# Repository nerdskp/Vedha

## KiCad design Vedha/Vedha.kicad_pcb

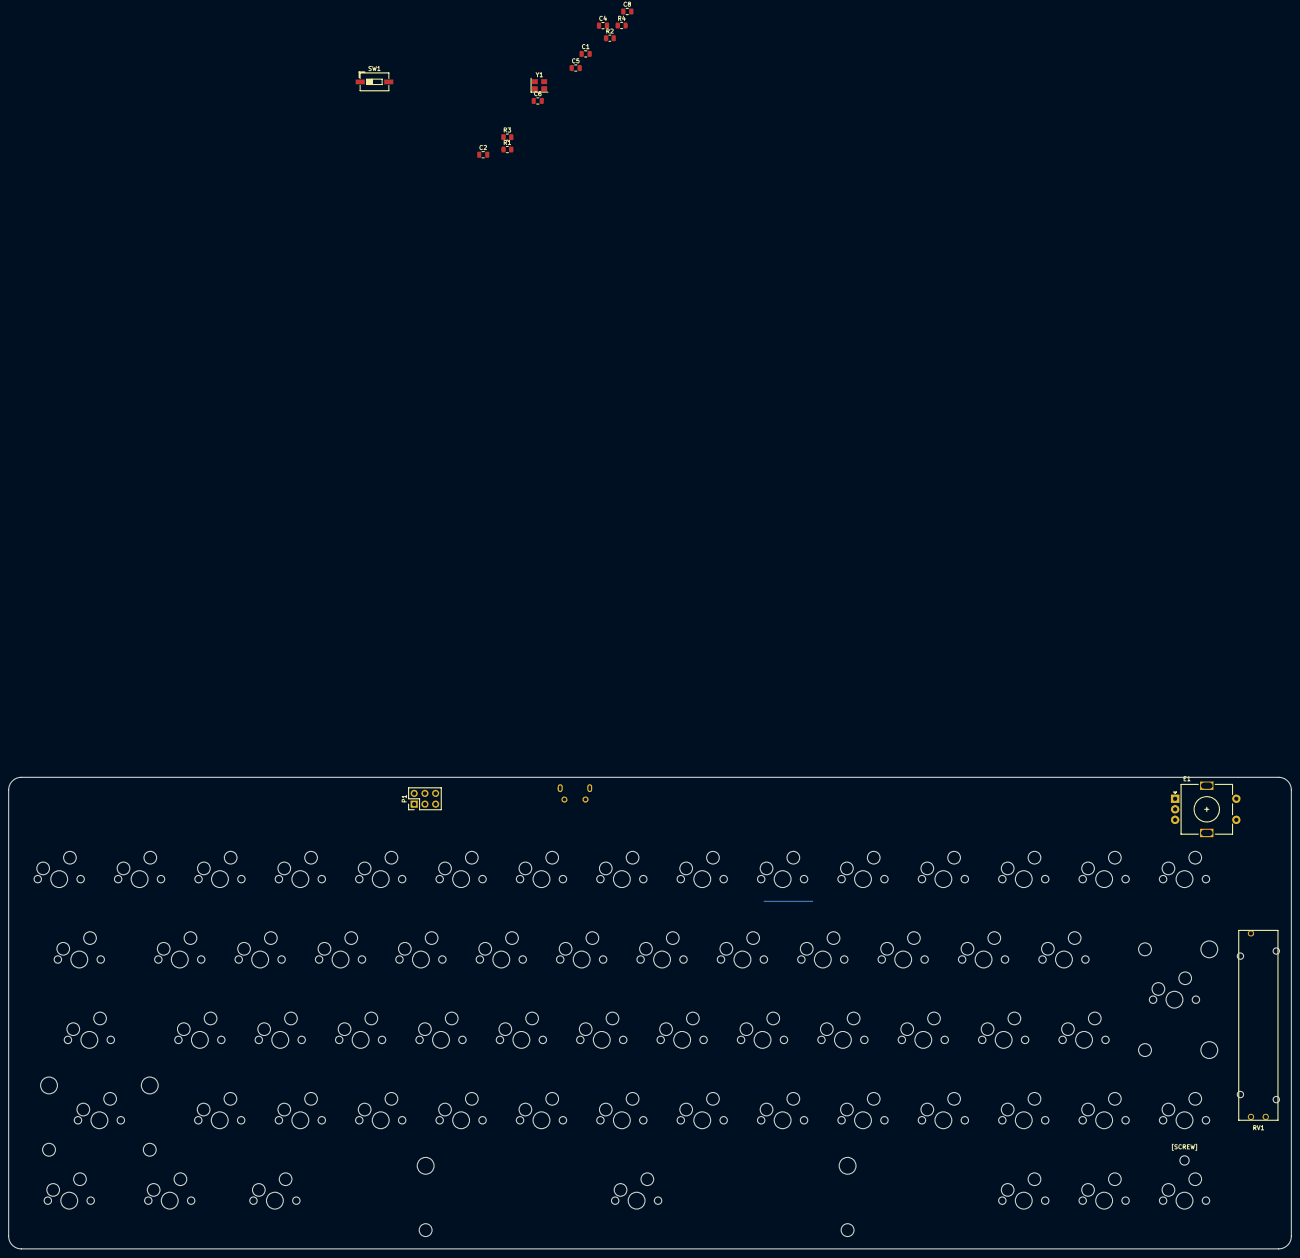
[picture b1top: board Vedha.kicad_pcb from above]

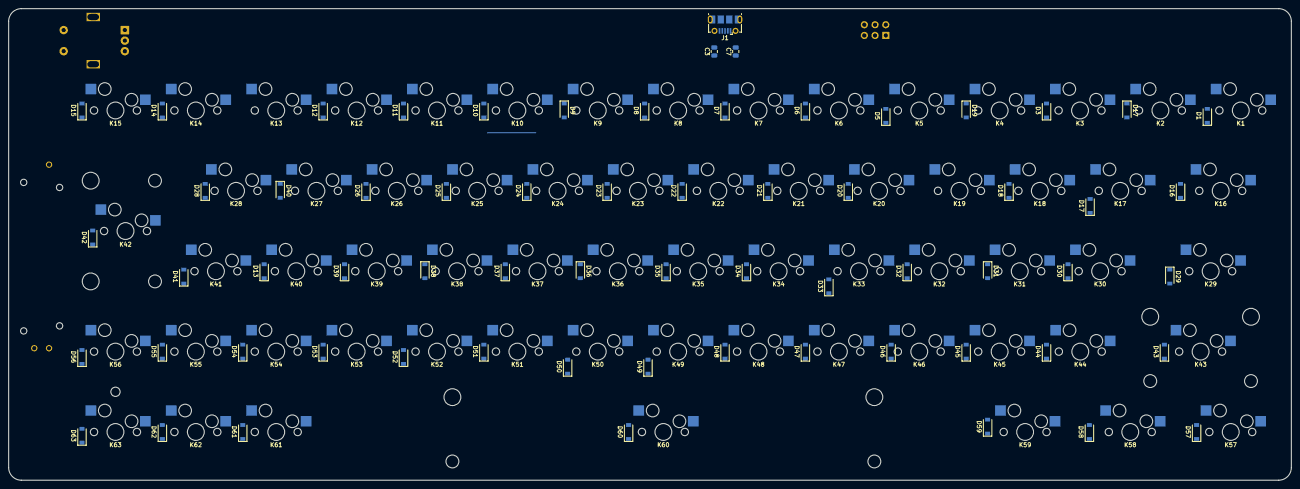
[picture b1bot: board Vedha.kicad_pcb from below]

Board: 2 copper layers, 304.0 x 111.8 mm, 143 parts (64 on the bottom side), 72 nets.

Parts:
C1, C2: 22p; C_0805_2012Metric
C3: 1u; C_0805_2012Metric
C4: 4.7u; C_0805_2012Metric
C5, C6, C7, C8: 100n; C_0805_2012Metric
D1, D3, D5, D6, D7, D8, D9, D10, D11, D12, D13, D14, D15, D16, D17, D17#2, D18, D19, D20, D21, D22, D23, D24, D25, D26, D28, D29, D30, D31, D32, D33, D34, D35, D36, D37, D38, D39, D40, D41, D42, D43, D44, D45, D46, D47, D48, D49, D50, D51, D52, D53, D54, D55, D56, D57, D58, D59, D60, D61, D62, D63: D; D_SOD-123
E1: Rotary_Encoder_Switch; RotaryEncoder_Alps_EC11E-Switch_Vertical_H20mm
J1: USB_B_Micro; USB_Micro-B_Molex-105017-0001
K1, K2, K3, K4, K5, K6, K7, K8, K9, K10, K11, K12, K13, K14, K15, K17, K18, K19, K20, K21, K22, K23, K24, K25, K26, K27, K28, K30, K31, K32, K33, K34, K35, K36, K37, K38, K39, K40, K41, K44, K45, K46, K47, K48, K49, K50, K51, K52, K53, K54, K55, K56, K61, K62, K63: KEYSW; MXOnly-1U-Hotswap
K16: KEYSW; MXOnly-1.5U-Hotswap
K29: KEYSW; MXOnly-1.75U-Hotswap
K42: KEYSW; MXOnly-ISO-Hotswap
K43: KEYSW; MXOnly-2U-Hotswap-ReversedStabilizers
K57, K58, K59: KEYSW; MXOnly-1.25U-Hotswap
K60: KEYSW; MXOnly-6.25U-Hotswap-ReversedStabilizers
P1: AVR-ISP-6; PinHeader_2x03_P2.54mm_Vertical
R1, R4: 10k; R_0805_2012Metric
R2, R3: 22; R_0805_2012Metric
RV1: R_POT; potentiometer_slider_45mm
SW1: SW_PUSH; SW_DIP_SPSTx01_Slide_6.7x4.1mm_W6.73mm_P2.54mm_LowProfile_J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
Y1: Crystal_GND24; Crystal_SMD_3225-4Pin_3.2x2.5mm
[SCREW]: MountingHole_2.2mm_M2

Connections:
GND: C1.1, C2.1, C3.1, C4.1, C5.1, C6.1, C7.1, C8.1, E1.C, J1.5 (GND), J1.6 (Shield), P1.6 (GND), R4.1, RV1.1, SW1.1, Y1.2, Y1.4
MISO_ROW0: D1.1 (K), D5.1 (K), D8.1 (K), D12.1 (K), D17#2.1 (K), D21.1 (K), D25.1 (K), D30.1 (K), D34.1 (K), D38.1 (K), D42.1 (K), D46.1 (K), D55.1 (K), D60.1 (K), P1.1 (MISO)
MOSI_ROW1: D9.1 (K), D13.1 (K), D17.1, D18.1 (K), D22.1 (K), D26.1 (K), D31.1 (K), D35.1 (K), D39.1 (K), D43.1 (K), D47.1 (K), D51.1 (K), D56.1 (K), P1.4 (MOSI)
unnamed: D1.2 (A), K1.2
unnamed: D3.2 (A), K3.2
unnamed: D5.2 (A), K5.2
unnamed: D6.2 (A), K6.2
unnamed: D7.2 (A), K7.2
unnamed: D8.2 (A), K8.2
unnamed: D9.2 (A), K9.2
unnamed: D10.2 (A), K10.2
unnamed: D11.2 (A), K11.2
unnamed: D12.2 (A), K12.2
unnamed: D13.2 (A), K13.2
unnamed: D14.2 (A), K14.2
unnamed: D15.2 (A), K15.2
unnamed: D16.2 (A), K16.2
unnamed: D17.2, D17#2.2 (A), K17.2
unnamed: D18.2 (A), K18.2
unnamed: D19.2 (A), K19.2
unnamed: D20.2 (A), K20.2
unnamed: D21.2 (A), K21.2
unnamed: D22.2 (A), K22.2
unnamed: D23.2 (A), K23.2
unnamed: D24.2 (A), K24.2
unnamed: D25.2 (A), K25.2
unnamed: D26.2 (A), K26.2
unnamed: D28.2 (A), K28.2
unnamed: D29.2 (A), K29.2
unnamed: D30.2 (A), K30.2
unnamed: D31.2 (A), K31.2
unnamed: D32.2 (A), K32.2
unnamed: D33.2, K33.2
unnamed: D34.2 (A), K34.2
unnamed: D35.2 (A), K35.2
unnamed: D36.2 (A), K36.2
unnamed: D37.2 (A), K37.2
unnamed: D38.2 (A), K38.2
unnamed: D39.2 (A), K39.2
unnamed: D40.2 (A), K40.2
unnamed: D41.2 (A), K41.2
unnamed: D42.2 (A), K42.2
unnamed: D43.2 (A), K43.2
unnamed: D44.2 (A), K44.2
unnamed: D45.2 (A), K45.2
unnamed: D46.2 (A), K46.2
unnamed: D47.2 (A), K47.2
unnamed: D48.2 (A), K48.2
unnamed: D49.2, K49.2
unnamed: D50.2, K50.2
unnamed: D51.2 (A), K51.2
unnamed: D52.2 (A), K52.2
unnamed: D53.2 (A), K53.2
unnamed: D54.2 (A), K54.2
unnamed: D55.2 (A), K55.2
unnamed: D56.2 (A), K56.2
unnamed: D57.2 (A), K57.2
unnamed: D58.2 (A), K58.2
unnamed: D59.2, K59.2
unnamed: D60.2 (A), K60.2
unnamed: D61.2 (A), K61.2
unnamed: D62.2 (A), K62.2
unnamed: D63.2 (A), K63.2
unnamed: J1.2 (D-), R2.2
unnamed: J1.3 (D+), R3.2
ROW3: D6.1 (K), D11.1 (K), D15.1 (K), D20.1 (K), D24.1 (K), D28.1 (K), D37.1 (K), D41.1 (K), D45.1 (K), D49.1, D50.1, D53.1 (K), D58.1 (K), D62.1 (K)
ROW4: D7.1 (K), D16.1 (K), D29.1 (K), D54.1 (K), D59.1, D63.1 (K)
RST: P1.5 (~RST), R1.1, SW1.2
SCK_ROW2: D3.1 (K), D10.1 (K), D14.1 (K), D19.1 (K), D23.1 (K), D32.1 (K), D33.1, D36.1 (K), D40.1 (K), D44.1 (K), D48.1 (K), D52.1 (K), D57.1 (K), D61.1 (K), P1.3 (SCK)
VCC: C4.2, C5.2, C6.2, C7.2, C8.2, J1.1 (VBUS), P1.2 (VCC), R1.2, RV1.3
XTAL1: C2.2, Y1.3
XTAL2: C1.2, Y1.1
